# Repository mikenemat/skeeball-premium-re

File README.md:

# skeeball-premium-re

Reverse engineering of the Bay Tek **Skee-Ball Home Arcade Premium** electronics, and an open replacement for its main
board (A5CB25502 Rev 2.2).

The replacement board, **SBC-1**, is a drop-in swap: the same outline, mounting holes and harness connector positions as
the stock board, so the machine's existing wiring plugs straight in. On top of the stock functions it adds wired
Ethernet, so several lanes can share high scores and play together.

| Folder | What |
|---|---|
| [`hardware/`](hardware/) | SBC-1: KiCad 10 project, design-as-code scripts, BOM, routed 4-layer board, manufacturing files, design records |
| [software/](software/) | ARM image-analysis tools and synthetic tests |

## SBC-1 at a glance
- **MCU:** Raspberry Pi RP2350B with 16 MB QSPI flash.
- **Network:** WIZnet W5500 10/100 Ethernet (HanRun magjack).
- **Audio:** MAX98357A I2S class-D amplifier to the stock speaker.
- **Display:** USB host port for the stock score display.
- **Lights:** PWM low-side drivers on the existing RGB and playfield LED strips.
- **Power:** protected 5 V input (TVS, eFuse, resettable fuses).
- **Debug:** USB-C serial console and SWD.
- **Setup:** lane-ID DIP switch, status LEDs.
- **PCB:** 4-layer, 116.68 x 85.73 mm, assembled by JLCPCB (all parts from JLC stock).

**Status:** the first batch of boards is in production. Firmware for the new board is an original implementation and
is not published yet. See [`hardware/README.md`](hardware/README.md) for the project layout, how to regenerate
everything, and what is deliberately not in the repository. See [`hardware/docs/BRINGUP.md`](hardware/docs/BRINGUP.md)
for first power-up.

## Notes
- This is an independent hobby project. It is not affiliated with or endorsed by Bay Tek Entertainment. Skee-Ball is a
  trademark of its owner.
- The tracked repository contains no Bay Tek firmware, binaries or decompiled code. Stock-board facts here come from
  measurements, photos and continuity tests of the owner's own machines.
- Third-party datasheets and vendor 3D models are not redistributed. The setup notes in `hardware/README.md` say
  how to fetch them.

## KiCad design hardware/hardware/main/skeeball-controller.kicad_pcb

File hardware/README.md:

# SBC-1 - Skee-Ball lane controller

Networked drop-in replacement for the Bay Tek **A5CB25502 Rev 2.2** main board of the Skee-Ball Home Arcade Premium:
RP2350B + 16 MB QSPI flash, WIZnet W5500 wired Ethernet, MAX98357A I2S class-D audio, USB host port for the stock
display, protected 5 V input (TVS + eFuse), PWM light drivers, USB-C debug console, lane-ID DIP. Same outline, holes and
harness connector positions as the stock board.

**Status (2026-10-29):** ordered. Five boards are in production at JLCPCB (4-layer, Economic PCBA). The KiCad board in
`hardware/main/` is the build: routed with 0 open connections and DRC clean. `fab/release-2026-10-27c/` is the
manufacturing record (Gerbers, drills, JLC BOM and CPL). Bring-up instructions are in `docs/BRINGUP.md`. The firmware is
a separate, original implementation (not in this folder yet).

| Path | What |
|---|---|
| `docs/ARCHITECTURE.md` | requirements, I/O + GPIO map, MCU comparison, every block's reference + deviations, cost |
| `docs/MEASUREMENTS_NEEDED.md` | the caliper measurements / confirmations the layout needs |
| `docs/PLACEMENT_PLAN.md` | footprints, function groups, the RJ45 zone study |
| `docs/ORDERING.md` | BOM with LCSC codes, JLC stock, price, check date (generated) |
| `docs/WORK_STATE.md` | live state + next steps; `RUNNING-LOG.md`, `QA_LOG.md`, `DECISIONS.md` |
| `scripts/design.py` | design of record (parts, nets, references) |
| `hardware/main/` | KiCad 10 project: generated schematic (6 sheets) and the routed 4-layer board |
| `hardware/lib/` | project symbols (`skeeball.kicad_sym`) and footprints (`skeeball.pretty`) |
| `bom/bom.json`, `bom/bom.html` | single-writer BOM + viewer (`python -m http.server` in `bom/`, open bom.html) |
| `renders/` | schematic PDF, footprint / placement renders, final board renders (`renders/pcb/final-2026-10-27b/`) |
| `fab/release-2026-10-27c/` | manufacturing record: Gerber + drill zip, JLC BOM, JLC CPL (rotations fitted to JLC footprints) |
| `tools/pfr2/` | the autorouter and its gate / cleanup tools used for the copper |
| `datasheets/` | vendor documents used (not committed: download them from the manufacturers) |

## Setup (what is not in the repository)
These are git-ignored, because they are third-party, machine-specific or regenerable:
- `datasheets/`: manufacturer PDFs referenced in `design.py` notes and `docs/ARCHITECTURE.md`. Download them from the
  vendors.
- `hardware/lib/3d/vendor/`: the vendor STEP models. `python scripts/vendor_models.py` fetches them by JLC part number.
  The project's own envelope models (`hardware/lib/3d/*.wrl`) are committed.
- `tools/pylib/`: shapely + numpy for KiCad's bundled Python (KiCad 10 ships without shapely). Install them with
  `"C:/Program Files/KiCad/10.0/bin/python.exe" -m pip install --target tools/pylib shapely==2.1.2 numpy`.
- `bom/.jlc_api_cache/`, `bom/easyeda_cache/`: JLC / EasyEDA API caches, rebuilt on demand.
- `.runtime/`: router runs, gate outputs, scratch boards and backups.
- `scripts/scan_extract.py` needs the 300 dpi scan of the stock board's bottom side (not published). Set `SKEEBALL_SCAN`
  to its path. Its measured output is committed in `docs/records/scan_extract/`.

Tool versions: KiCad 10.0.6 (kicad-cli + its Python for `pcbnew` scripts), CPython 3.13 with numpy, scipy, pillow,
shapely, cairosvg and kicad-sch-api 0.5.5.

## Regenerate (CPython 3.13, KiCad 10.0.6)
```
cd scripts
python symgen.py                 # hardware/lib/skeeball.kicad_sym
python build_schematics.py       # schematic + KiCad ERC gate + netlist compare against design.py
python qa_footprints.py          # every footprint resolves (or is listed as pending with its reason)
python bom.py build && python bom.py refresh && python bom.py check && python bom.py report
python mcu_survey.py             # MCU option prices (docs/records/mcu_survey)
python fpgen.py                  # hardware/lib/skeeball.pretty (project footprints)
python scan_extract.py           # harness pad centres from the owner's 300 dpi bottom scan -> docs/records/scan_extract
python jlc_footprints.py C...     # JLC / EasyEDA footprint of a C-number -> bom/easyeda_cache (footprint cross-check)
python model_gen.py              # envelope 3D models for footprints without a KiCad model -> hardware/lib/3d
python photo_estimate.py && python render_placement.py   # placement plan + RJ45 study renders
python pcb_build.py              # board file: measured outline + 4 holes (+ SVG / PNG render)
"C:/Program Files/KiCad/10.0/bin/python.exe" place.py   # netlist import + placement + silk labels + KiCad DRC
"C:/Program Files/KiCad/10.0/bin/kicad-cli.exe" sch export pdf -o ../renders/schematic/skeeball-controller-schematic.pdf ../hardware/main/skeeball-controller.kicad_sch
```
Scripts reused from the owner's earlier din-relay-8ch project: `jlc_api.py` (unchanged), `netlist_core.py`, `gen_schematic.py`,
`qa_netlist.py`, `symgen.py` (library name / label direction / field placement adapted), the build -> ERC -> netlist QA
flow and the one-JSON / one-writer BOM.

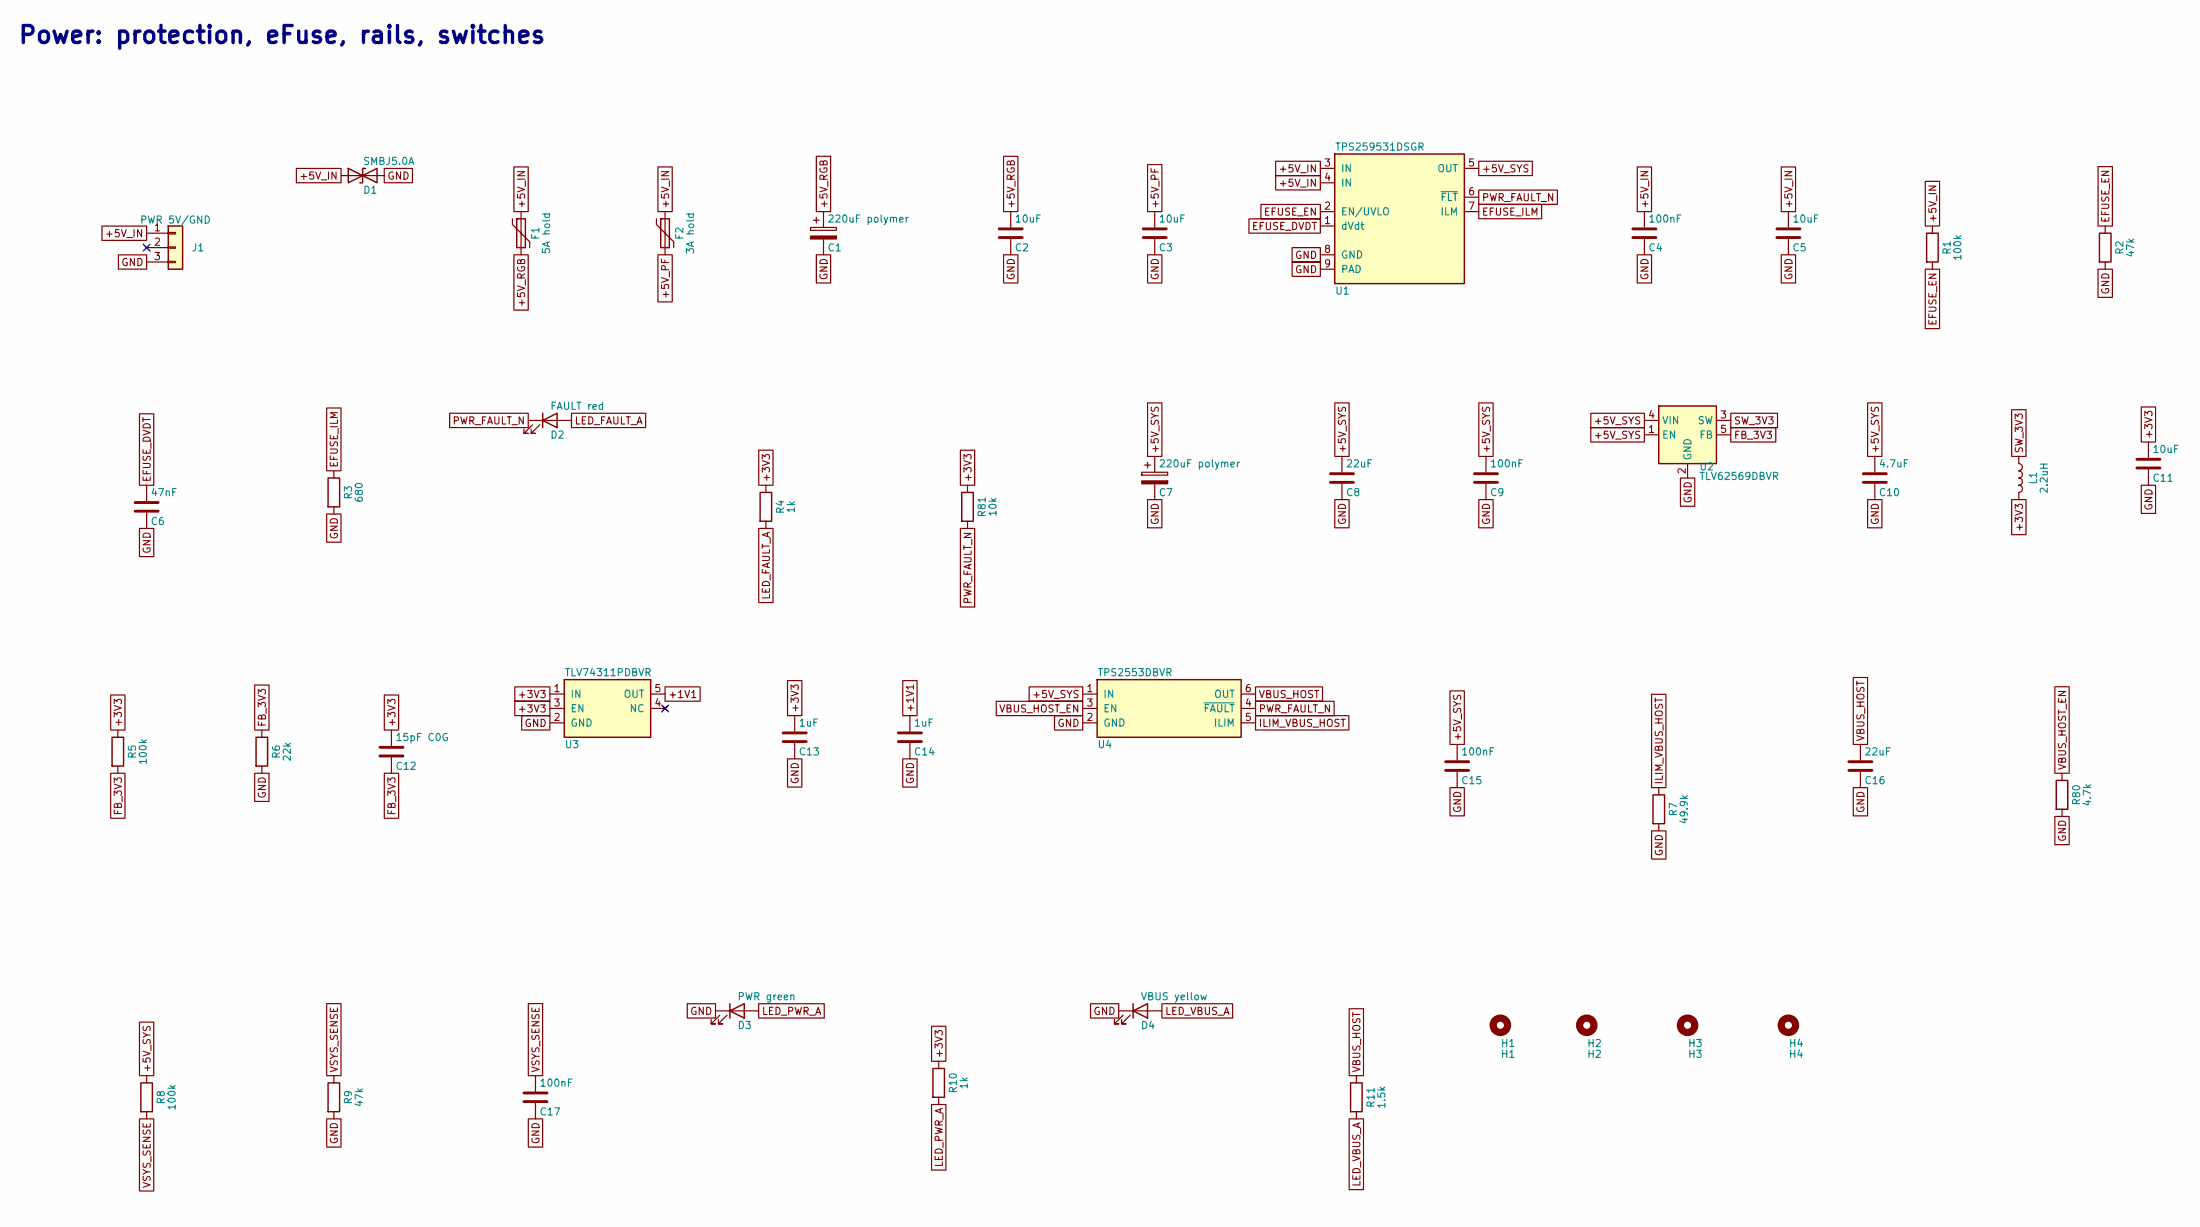
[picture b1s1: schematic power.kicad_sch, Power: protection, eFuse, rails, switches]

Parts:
C1, C7: 220uF polymer; CP_Elec_6.3x5.9; MPN OVZ221M1ATR-0606
C2, C3, C5, C11: 10uF; C_0805_2012Metric; MPN CL21A106KAYNNNE
C4, C9, C15, C17: 100nF; C_0603_1608Metric; MPN CC0603KRX7R9BB104
C6: 47nF; C_0603_1608Metric; MPN CL10B473KB8NNNC
C8, C16: 22uF; C_0805_2012Metric; MPN CL21A226MAQNNNE
C10: 4.7uF; C_0805_2012Metric; MPN CL21A475KAQNNNE
C12: 15pF C0G; C_0603_1608Metric; MPN CL10C150JB8NNNC
C13, C14: 1uF; C_0603_1608Metric; MPN CL10A105KB8NNNC
D1: SMBJ5.0A; D_SMB; MPN SMBJ5.0A; LCSC C83333
D2: FAULT red; LED_0603_1608Metric; MPN KT-0603R; LCSC C2286
D3: PWR green; LED_0603_1608Metric; MPN KT-0603G; LCSC C12624
D4: VBUS yellow; LED_0603_1608Metric; MPN NCD0603Y1; LCSC C84268
F1: 5A hold; Fuse_2920_7451Metric; MPN 2920L500/16MR; LCSC C207091
F2: 3A hold; Fuse_1812_4532Metric; MPN 1812L300MR; LCSC C127824
H1: H1; MountingHole_3.57mm
H2: H2; MountingHole_3.57mm
H3: H3; MountingHole_3.57mm
H4: H4; MountingHole_3.57mm
J1: PWR 5V/GND; Molex_Mini-Fit_Jr_39-30-3035_1x03_P4.20mm_Horizontal; MPN 39303035; LCSC C505179
L1: 2.2uH; L_Sunlord_SWPA4030S; MPN SWPA4030S2R2MT; LCSC C36409
R1, R5, R8: 100k; R_0603_1608Metric; tolerance 1%; MPN 0603WAF1003T5E
R2, R9: 47k; R_0603_1608Metric; tolerance 1%; MPN 0603WAF4702T5E
R3: 680; R_0603_1608Metric; tolerance 1%; MPN 0603WAF6800T5E
R4, R10: 1k; R_0603_1608Metric; tolerance 1%; MPN 0603WAF1001T5E
R6: 22k; R_0603_1608Metric; tolerance 1%; MPN 0603WAF2202T5E
R7: 49.9k; R_0603_1608Metric; tolerance 1%; MPN 0603WAF4992T5E
R11: 1.5k; R_0603_1608Metric; tolerance 1%; MPN 0603WAF1501T5E
R80: 4.7k; R_0603_1608Metric; tolerance 1%; MPN 0603WAF4701T5E
R81: 10k; R_0603_1608Metric; tolerance 1%; MPN 0603WAF1002T5E
U1: TPS259531DSGR; Texas_DSG0008A_WSON-8-1EP_2x2mm_P0.5mm_EP0.9x1.6mm; MPN TPS259531DSGR; LCSC C2155674
U2: TLV62569DBVR; SOT-23-5; MPN TLV62569DBVR; LCSC C141836
U3: TLV74311PDBVR; SOT-23-5; MPN TLV74311PDBVR; LCSC C485147
U4: TPS2553DBVR; SOT-23-6; MPN TPS2553DBVR; LCSC C55266

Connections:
+1V1: C14.1, U3.5 (OUT); also elsewhere on the board
+3V3: C11.1, C12.1, C13.1, L1.2, R4.1, R5.1, R10.1, R81.1, U3.1 (IN), U3.3 (EN); also elsewhere on the board
+5V_IN: C4.1, C5.1, D1.1 (A1), F1.1, F2.1, J1.1, R1.1, U1.3 (IN), U1.4 (IN)
+5V_PF: C3.1, F2.2; also elsewhere on the board
+5V_RGB: C1.1, C2.1, F1.2; also elsewhere on the board
+5V_SYS: C7.1, C8.1, C9.1, C10.1, C15.1, R8.1, U1.5 (OUT), U2.1 (EN), U2.4 (VIN), U4.1 (IN); also elsewhere on the board
EFUSE_DVDT: C6.1, U1.1 (dVdt)
EFUSE_EN: R1.2, R2.1, U1.2 (EN/UVLO)
EFUSE_ILM: R3.1, U1.7 (ILM)
FB_3V3: C12.2, R5.2, R6.1, U2.5 (FB)
GND: C1.2, C2.2, C3.2, C4.2, C5.2, C6.2, C7.2, C8.2, C9.2, C10.2, C11.2, C13.2, C14.2, C15.2, C16.2, C17.2, D1.2 (A2), D3.1 (K), D4.1 (K), J1.3, R2.2, R3.2, R6.2, R7.2, R9.2, R80.2, U1.8 (GND), U1.9 (PAD), U2.2 (GND), U3.2 (GND), U4.2 (GND); also elsewhere on the board
ILIM_VBUS_HOST: R7.1, U4.5 (ILIM)
LED_FAULT_A: D2.2 (A), R4.2
LED_PWR_A: D3.2 (A), R10.2
LED_VBUS_A: D4.2 (A), R11.2
PWR_FAULT_N: D2.1 (K), R81.2, U1.6 (~FLT), U4.4 (~FAULT); also elsewhere on the board
SW_3V3: L1.1, U2.3 (SW)
VBUS_HOST: C16.1, R11.1, U4.6 (OUT); also elsewhere on the board
VBUS_HOST_EN: R80.1, U4.3 (EN); also elsewhere on the board
VSYS_SENSE: C17.1, R8.2, R9.1; also elsewhere on the board

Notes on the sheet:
Power: protection, eFuse, rails, switches

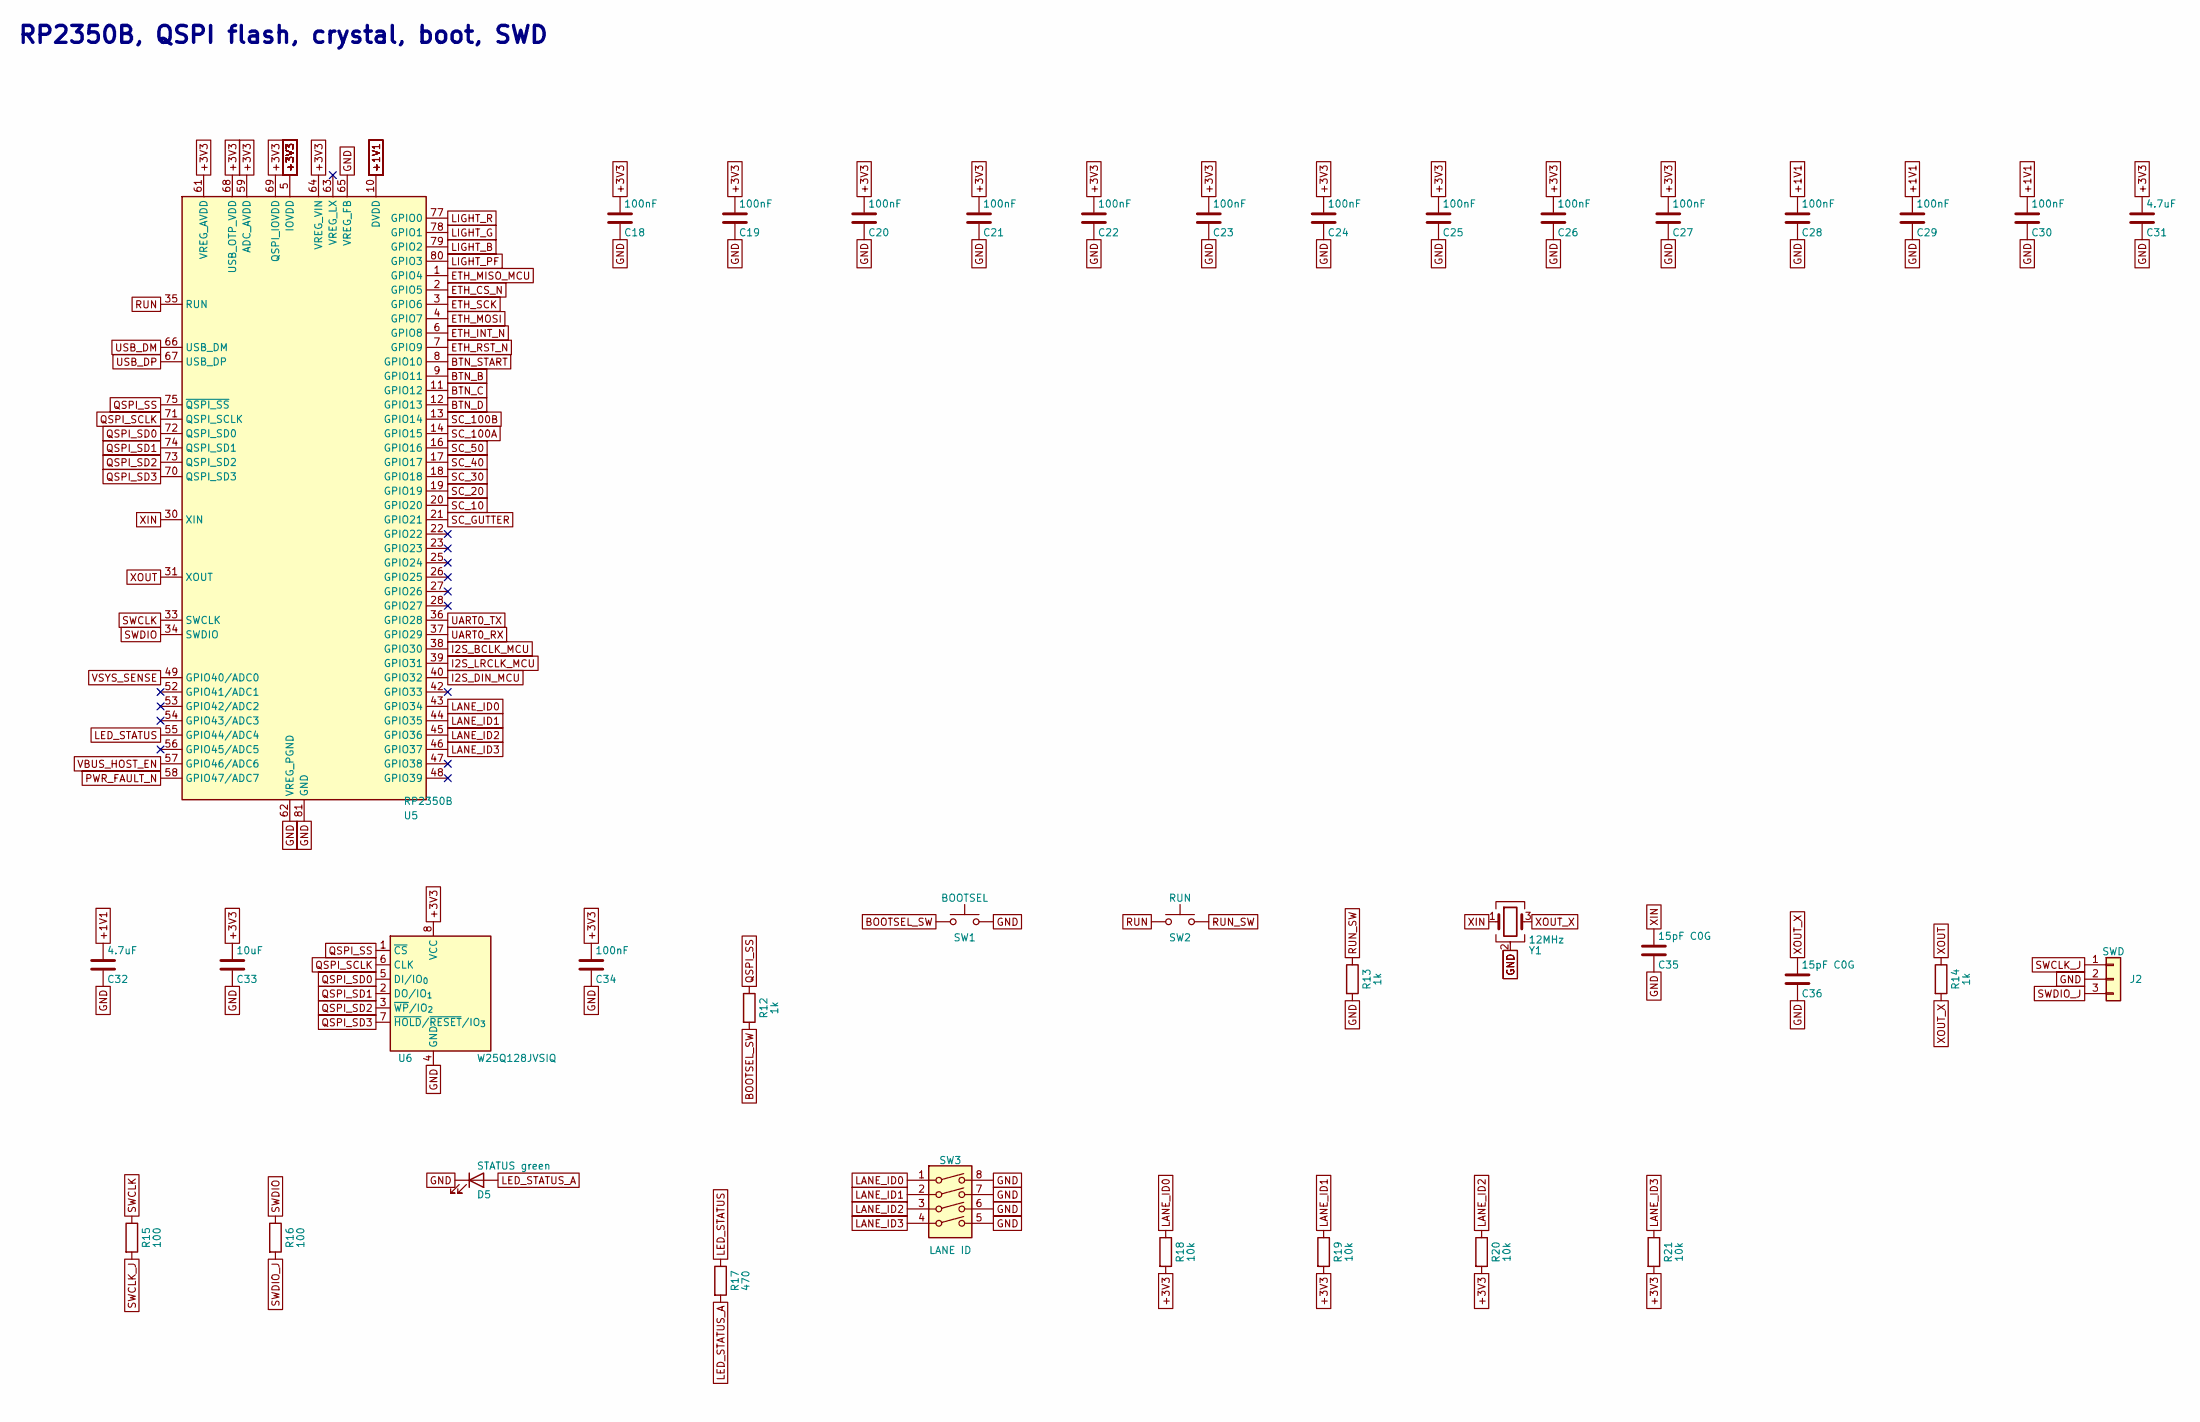
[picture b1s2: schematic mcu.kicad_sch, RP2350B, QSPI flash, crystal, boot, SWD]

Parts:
C18, C19, C20, C21, C22, C23, C24, C25, C26, C27, C28, C29, C30, C34: 100nF; C_0402_1005Metric; MPN CL05B104KO5NNNC
C31, C32: 4.7uF; C_0402_1005Metric; MPN CL05A475MP5NRNC
C33: 10uF; C_0805_2012Metric; MPN CL21A106KAYNNNE
C35, C36: 15pF C0G; C_0603_1608Metric; MPN CL10C150JB8NNNC
D5: STATUS green; LED_0603_1608Metric; MPN KT-0603G; LCSC C12624
J2: SWD; JST_SH_BM03B-SRSS-TB_1x03-1MP_P1.00mm_Vertical; MPN BM03B-SRSS-TB(LF)(SN); LCSC C160389
R12, R13, R14: 1k; R_0402_1005Metric; tolerance 1%; MPN 0402WGF1001TCE
R15, R16: 100; R_0402_1005Metric; tolerance 1%; MPN 0402WGF1000TCE
R17: 470; R_0603_1608Metric; tolerance 1%; MPN 0603WAF4700T5E
R18, R19, R20, R21: 10k; R_0603_1608Metric; tolerance 1%; MPN 0603WAF1002T5E
SW1: BOOTSEL; SW_Push_1P1T_XKB_TS-1187A; MPN TS-1187A-B-A-B; LCSC C318884
SW2: RUN; SW_Push_1P1T_XKB_TS-1187A; MPN TS-1187A-B-A-B; LCSC C318884
SW3: LANE ID; SW_DIP_XKB_DSIC04LS-P; MPN DSIC04LS-P; LCSC C319038
U5: RP2350B; QFN-80-1EP_10x10mm_P0.4mm_EP3.4x3.4mm; MPN RP2350B; LCSC C42415655
U6: W25Q128JVSIQ; SOIC-8_5.3x5.3mm_P1.27mm; MPN W25Q128JVSIQ; LCSC C97521
Y1: 12MHz; Crystal_SMD_3225-4Pin_3.2x2.5mm; MPN ABM8-272-T3; LCSC C20625731

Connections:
+1V1: C28.1, C29.1, C30.1, C32.1, U5.10 (DVDD), U5.32 (DVDD), U5.51 (DVDD); also elsewhere on the board
+3V3: C18.1, C19.1, C20.1, C21.1, C22.1, C23.1, C24.1, C25.1, C26.1, C27.1, C31.1, C33.1, C34.1, R18.2, R19.2, R20.2, R21.2, U5.5 (IOVDD), U5.15 (IOVDD), U5.24 (IOVDD), U5.29 (IOVDD), U5.41 (IOVDD), U5.50 (IOVDD), U5.59 (ADC_AVDD), U5.60 (IOVDD), U5.61 (VREG_AVDD), U5.64 (VREG_VIN), U5.68 (USB_OTP_VDD), U5.69 (QSPI_IOVDD), U5.76 (IOVDD), U6.8 (VCC); also elsewhere on the board
BOOTSEL_SW: R12.2, SW1.1
BTN_B: U5.9 (GPIO11); also elsewhere on the board
BTN_C: U5.11 (GPIO12); also elsewhere on the board
BTN_D: U5.12 (GPIO13); also elsewhere on the board
BTN_START: U5.8 (GPIO10); also elsewhere on the board
ETH_CS_N: U5.2 (GPIO5); also elsewhere on the board
ETH_INT_N: U5.6 (GPIO8); also elsewhere on the board
ETH_MISO_MCU: U5.1 (GPIO4); also elsewhere on the board
ETH_MOSI: U5.4 (GPIO7); also elsewhere on the board
ETH_RST_N: U5.7 (GPIO9); also elsewhere on the board
ETH_SCK: U5.3 (GPIO6); also elsewhere on the board
GND: C18.2, C19.2, C20.2, C21.2, C22.2, C23.2, C24.2, C25.2, C26.2, C27.2, C28.2, C29.2, C30.2, C31.2, C32.2, C33.2, C34.2, C35.2, C36.2, D5.1 (K), J2.2, R13.2, SW1.2, SW3.5, SW3.6, SW3.7, SW3.8, U5.62 (VREG_PGND), U5.65 (VREG_FB), U5.81 (GND), U6.4 (GND), Y1.2 (G), Y1.4 (G); also elsewhere on the board
I2S_BCLK_MCU: U5.38 (GPIO30); also elsewhere on the board
I2S_DIN_MCU: U5.40 (GPIO32); also elsewhere on the board
I2S_LRCLK_MCU: U5.39 (GPIO31); also elsewhere on the board
LANE_ID0: R18.1, SW3.1, U5.43 (GPIO34)
LANE_ID1: R19.1, SW3.2, U5.44 (GPIO35)
LANE_ID2: R20.1, SW3.3, U5.45 (GPIO36)
LANE_ID3: R21.1, SW3.4, U5.46 (GPIO37)
LED_STATUS: R17.1, U5.55 (GPIO44/ADC4)
LED_STATUS_A: D5.2 (A), R17.2
LIGHT_B: U5.79 (GPIO2); also elsewhere on the board
LIGHT_G: U5.78 (GPIO1); also elsewhere on the board
LIGHT_PF: U5.80 (GPIO3); also elsewhere on the board
LIGHT_R: U5.77 (GPIO0); also elsewhere on the board
PWR_FAULT_N: U5.58 (GPIO47/ADC7); also elsewhere on the board
QSPI_SCLK: U5.71 (QSPI_SCLK), U6.6 (CLK)
QSPI_SD0: U5.72 (QSPI_SD0), U6.5 (DI/IO_{0})
QSPI_SD1: U5.74 (QSPI_SD1), U6.2 (DO/IO_{1})
QSPI_SD2: U5.73 (QSPI_SD2), U6.3 (~WP/IO_{2})
QSPI_SD3: U5.70 (QSPI_SD3), U6.7 (~HOLD/~RESET/IO_{3})
QSPI_SS: R12.1, U5.75 (~QSPI_SS), U6.1 (~CS)
RUN: SW2.1, U5.35 (RUN)
RUN_SW: R13.1, SW2.2
SC_10: U5.20 (GPIO20); also elsewhere on the board
SC_20: U5.19 (GPIO19); also elsewhere on the board
SC_30: U5.18 (GPIO18); also elsewhere on the board
SC_40: U5.17 (GPIO17); also elsewhere on the board
SC_50: U5.16 (GPIO16); also elsewhere on the board
SC_100A: U5.14 (GPIO15); also elsewhere on the board
SC_100B: U5.13 (GPIO14); also elsewhere on the board
SC_GUTTER: U5.21 (GPIO21); also elsewhere on the board
SWCLK: R15.1, U5.33 (SWCLK)
SWCLK_J: J2.1, R15.2
SWDIO: R16.1, U5.34 (SWDIO)
SWDIO_J: J2.3, R16.2
UART0_RX: U5.37 (GPIO29); also elsewhere on the board
UART0_TX: U5.36 (GPIO28); also elsewhere on the board
USB_DM: U5.66 (USB_DM); also elsewhere on the board
USB_DP: U5.67 (USB_DP); also elsewhere on the board
VBUS_HOST_EN: U5.57 (GPIO46/ADC6); also elsewhere on the board
VSYS_SENSE: U5.49 (GPIO40/ADC0); also elsewhere on the board
XIN: C35.1, U5.30 (XIN), Y1.1
XOUT: R14.1, U5.31 (XOUT)
XOUT_X: C36.1, R14.2, Y1.3

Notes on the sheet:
RP2350B, QSPI flash, crystal, boot, SWD

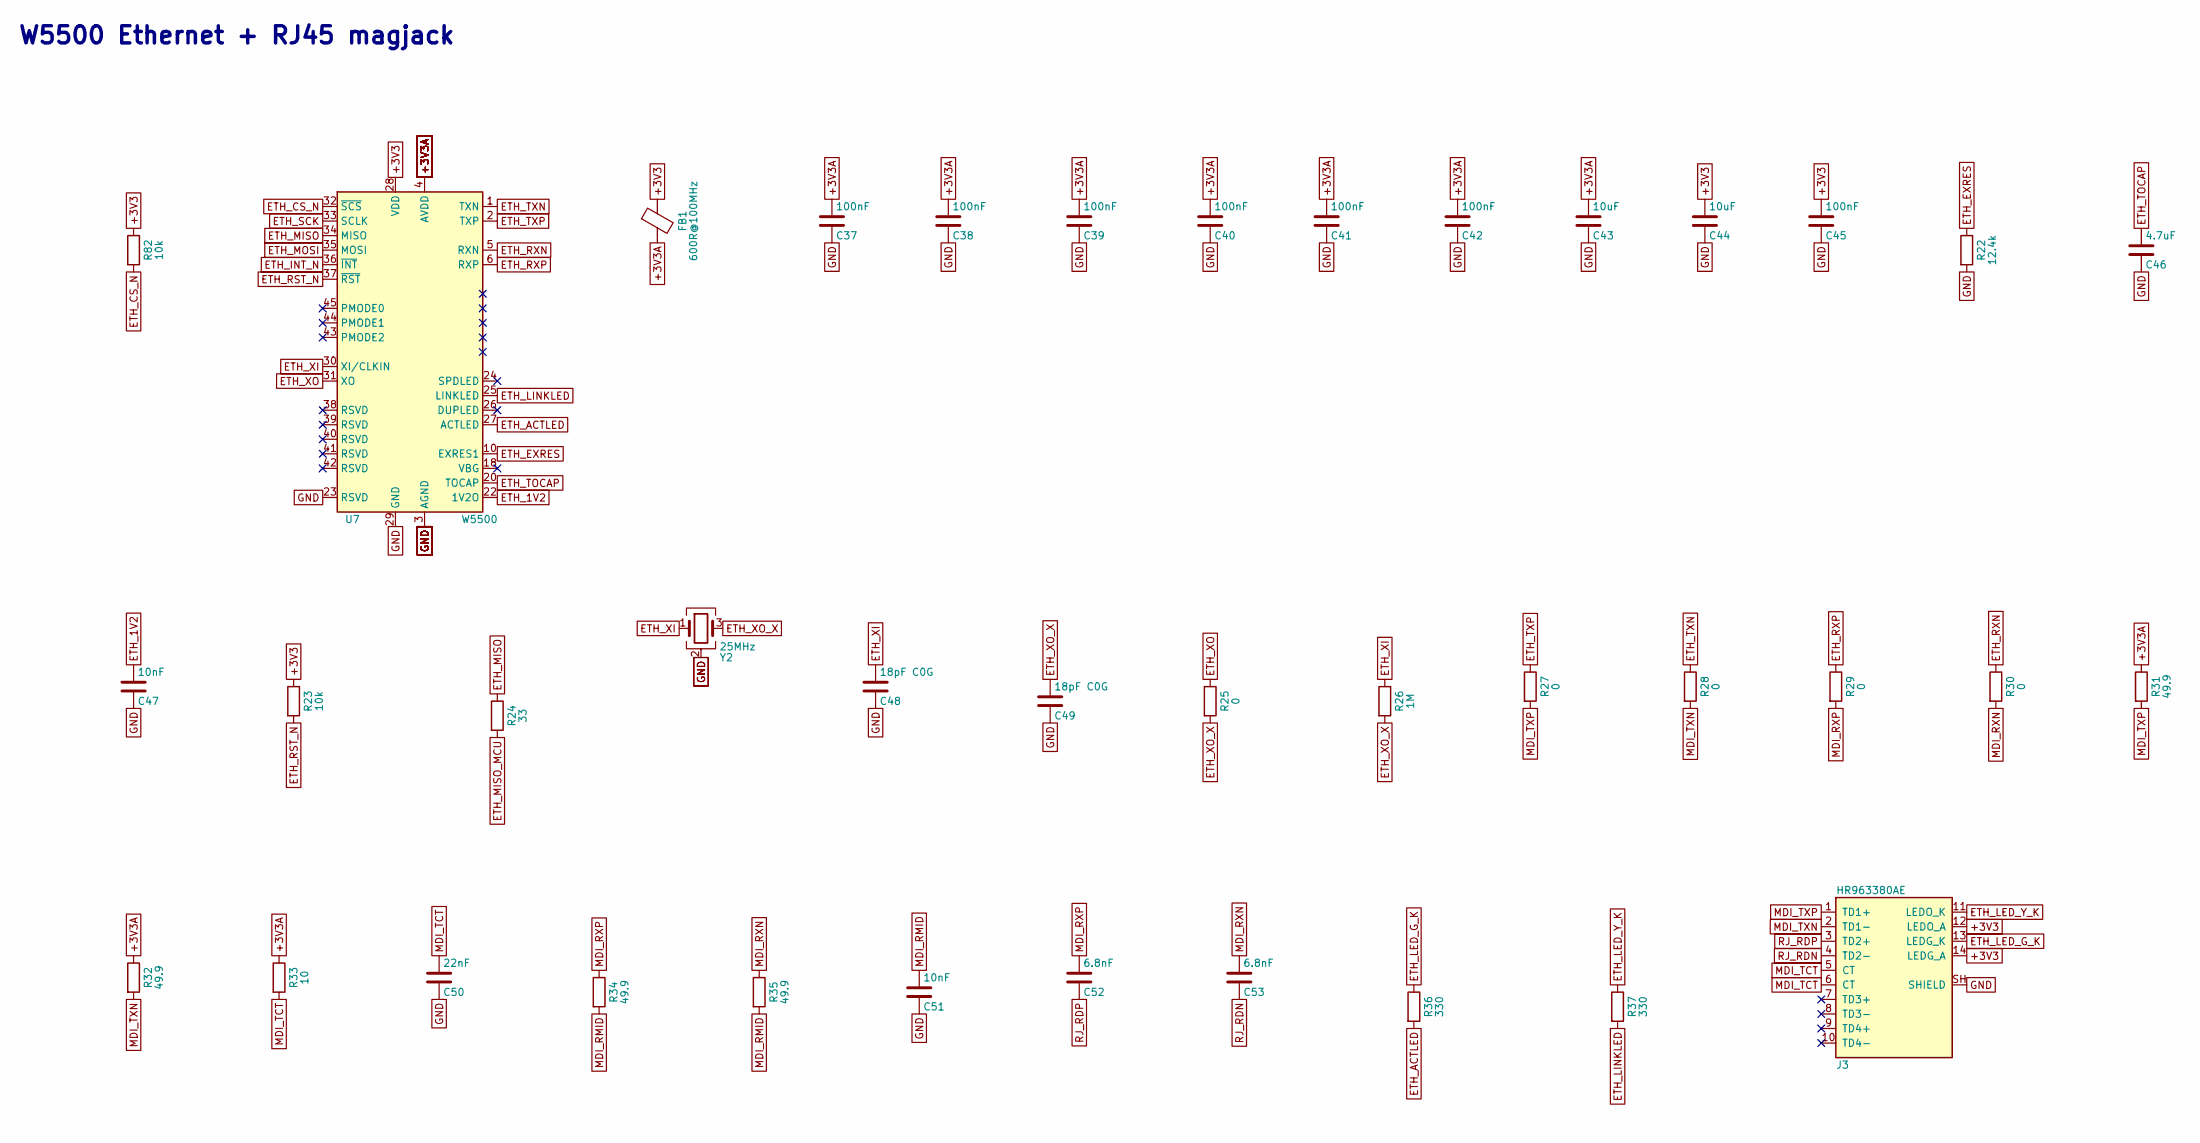
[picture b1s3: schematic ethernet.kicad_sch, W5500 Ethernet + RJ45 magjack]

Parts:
C37, C38, C39, C40, C41, C42, C45: 100nF; C_0603_1608Metric; MPN CC0603KRX7R9BB104
C43, C44: 10uF; C_0805_2012Metric; MPN CL21A106KAYNNNE
C46: 4.7uF; C_0805_2012Metric; MPN CL21A475KAQNNNE
C47, C51: 10nF; C_0603_1608Metric; MPN 0603B103K500NT
C48, C49: 18pF C0G; C_0603_1608Metric; MPN CL10C180JB8NNNC
C50: 22nF; C_0603_1608Metric; MPN CL10B223KB8NNNC
C52, C53: 6.8nF; C_0603_1608Metric; MPN 0603B682K500NT
FB1: 600R@100MHz; L_0805_2012Metric; MPN GZ2012D601TF; LCSC C1017
J3: HR963380AE; RJ45_HanRun_HR963380AE_Vertical; MPN HR963380AE; LCSC C19724763
R22: 12.4k; R_0603_1608Metric; tolerance 1%; MPN 0603WAF1242T5E
R23, R82: 10k; R_0603_1608Metric; tolerance 1%; MPN 0603WAF1002T5E
R24: 33; R_0603_1608Metric; tolerance 1%; MPN 0603WAF330JT5E
R25, R27, R28, R29, R30: 0; R_0603_1608Metric; tolerance 1%; MPN 0603WAF0000T5E
R26: 1M; R_0603_1608Metric; tolerance 1%; MPN 0603WAF1004T5E
R31, R32, R34, R35: 49.9; R_0603_1608Metric; tolerance 1%; MPN 0603WAF499JT5E
R33: 10; R_0603_1608Metric; tolerance 1%; MPN 0603WAF100JT5E
R36, R37: 330; R_0603_1608Metric; tolerance 1%; MPN 0603WAF3300T5E
U7: W5500; LQFP-48_7x7mm_P0.5mm; MPN W5500; LCSC C32843
Y2: 25MHz; Crystal_SMD_3225-4Pin_3.2x2.5mm; MPN X322525MOB4SI; LCSC C9006

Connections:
+3V3: C44.1, C45.1, FB1.1, J3.12 (LEDO_A), J3.14 (LEDG_A), R23.1, R82.1, U7.28 (VDD); also elsewhere on the board
+3V3A: C37.1, C38.1, C39.1, C40.1, C41.1, C42.1, C43.1, FB1.2, R31.1, R32.1, R33.1, U7.4 (AVDD), U7.8 (AVDD), U7.11 (AVDD), U7.15 (AVDD), U7.17 (AVDD), U7.21 (AVDD)
ETH_1V2: C47.1, U7.22 (1V2O)
ETH_ACTLED: R36.2, U7.27 (ACTLED)
ETH_CS_N: R82.2, U7.32 (~SCS); also elsewhere on the board
ETH_EXRES: R22.1, U7.10 (EXRES1)
ETH_INT_N: U7.36 (~INT); also elsewhere on the board
ETH_LED_G_K: J3.13 (LEDG_K), R36.1
ETH_LED_Y_K: J3.11 (LEDO_K), R37.1
ETH_LINKLED: R37.2, U7.25 (LINKLED)
ETH_MISO: R24.1, U7.34 (MISO)
ETH_MISO_MCU: R24.2; also elsewhere on the board
ETH_MOSI: U7.35 (MOSI); also elsewhere on the board
ETH_RST_N: R23.2, U7.37 (~RST); also elsewhere on the board
ETH_RXN: R30.1, U7.5 (RXN)
ETH_RXP: R29.1, U7.6 (RXP)
ETH_SCK: U7.33 (SCLK); also elsewhere on the board
ETH_TOCAP: C46.1, U7.20 (TOCAP)
ETH_TXN: R28.1, U7.1 (TXN)
ETH_TXP: R27.1, U7.2 (TXP)
ETH_XI: C48.1, R26.1, U7.30 (XI/CLKIN), Y2.1
ETH_XO: R25.1, U7.31 (XO)
ETH_XO_X: C49.1, R25.2, R26.2, Y2.3
GND: C37.2, C38.2, C39.2, C40.2, C41.2, C42.2, C43.2, C44.2, C45.2, C46.2, C47.2, C48.2, C49.2, C50.2, C51.2, J3.SH (SHIELD), R22.2, U7.3 (AGND), U7.9 (AGND), U7.14 (AGND), U7.16 (AGND), U7.19 (AGND), U7.23 (RSVD), U7.29 (GND), U7.48 (AGND), Y2.2 (G), Y2.4 (G); also elsewhere on the board
MDI_RMID: C51.1, R34.2, R35.2
MDI_RXN: C53.1, R30.2, R35.1
MDI_RXP: C52.1, R29.2, R34.1
MDI_TCT: C50.1, J3.5 (CT), J3.6 (CT), R33.2
MDI_TXN: J3.2 (TD1-), R28.2, R32.2
MDI_TXP: J3.1 (TD1+), R27.2, R31.2
RJ_RDN: C53.2, J3.4 (TD2-)
RJ_RDP: C52.2, J3.3 (TD2+)

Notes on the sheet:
W5500 Ethernet + RJ45 magjack

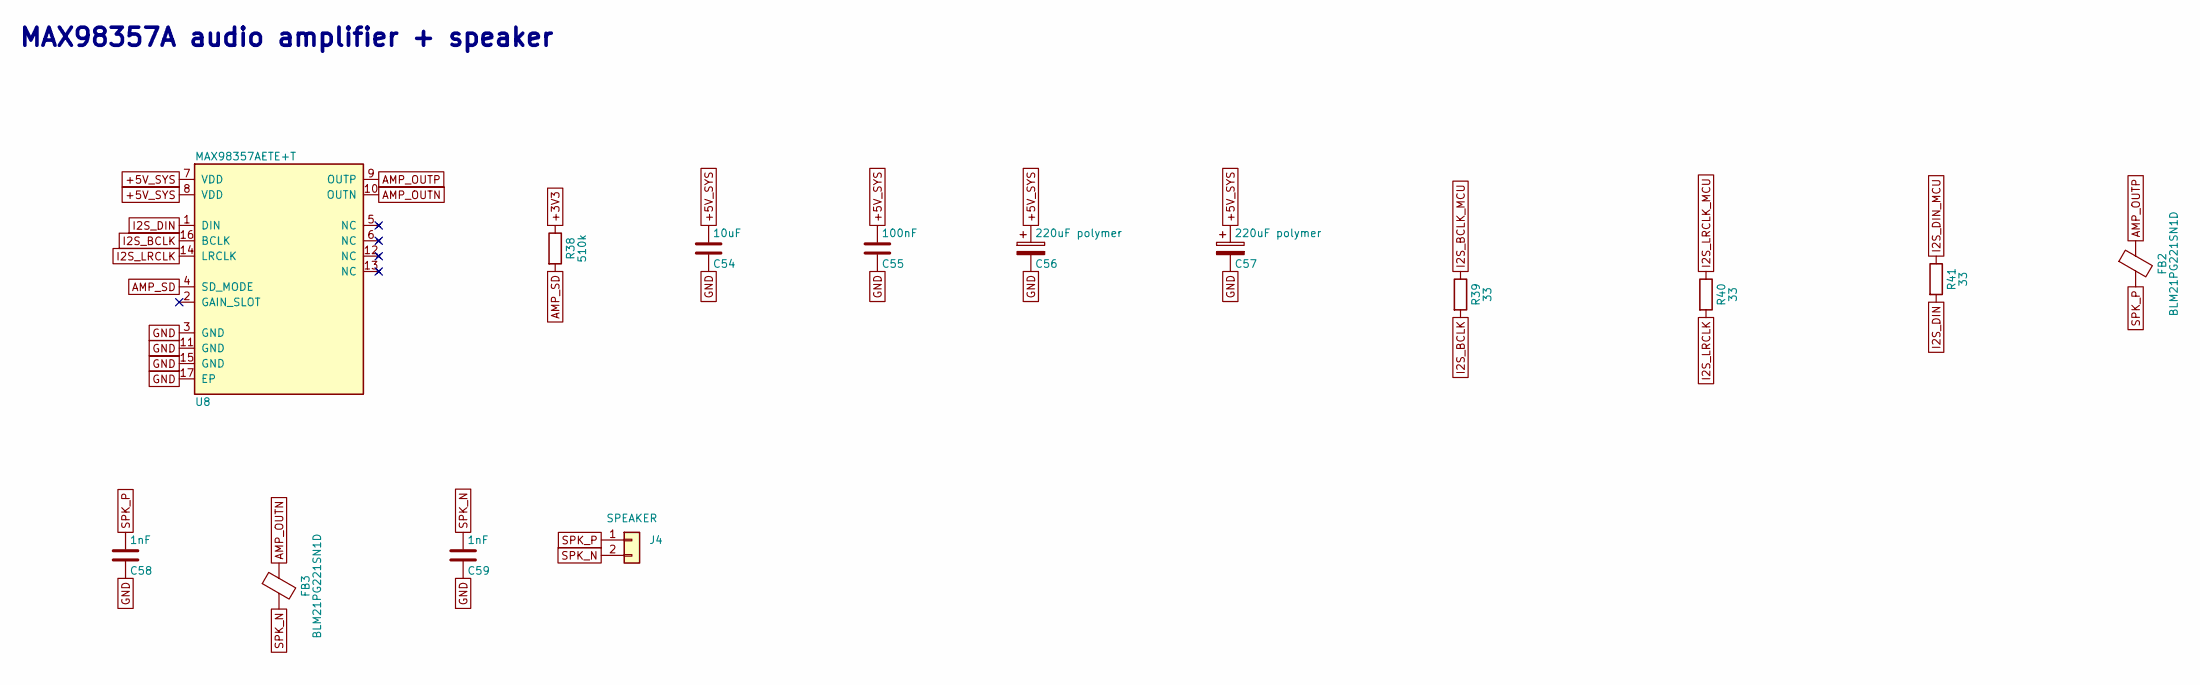
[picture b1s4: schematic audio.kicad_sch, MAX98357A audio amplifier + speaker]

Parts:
C54: 10uF; C_0805_2012Metric; MPN CL21A106KAYNNNE
C55: 100nF; C_0603_1608Metric; MPN CC0603KRX7R9BB104
C56, C57: 220uF polymer; CP_Elec_6.3x5.9; MPN OVZ221M1ATR-0606
C58, C59: 1nF; C_0603_1608Metric; MPN CL10B102KB8NNNC
FB2, FB3: BLM21PG221SN1D; L_0805_2012Metric; MPN BLM21PG221SN1D; LCSC C85840
J4: SPEAKER; Molex_Mini-Fit_Jr_5569-02A2_2x01_P4.20mm_Horizontal; MPN 39300020; LCSC C240831
R38: 510k; R_0603_1608Metric; tolerance 1%; MPN 0603WAF5103T5E
R39, R40, R41: 33; R_0603_1608Metric; tolerance 1%; MPN 0603WAF330JT5E
U8: MAX98357AETE+T; TQFN-16-1EP_3x3mm_P0.5mm_EP1.23x1.23mm; MPN MAX98357AETE+T; LCSC C910544

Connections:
+3V3: R38.1; also elsewhere on the board
+5V_SYS: C54.1, C55.1, C56.1, C57.1, U8.7 (VDD), U8.8 (VDD); also elsewhere on the board
AMP_OUTN: FB3.1, U8.10 (OUTN)
AMP_OUTP: FB2.1, U8.9 (OUTP)
AMP_SD: R38.2, U8.4 (SD_MODE)
GND: C54.2, C55.2, C56.2, C57.2, C58.2, C59.2, U8.3 (GND), U8.11 (GND), U8.15 (GND), U8.17 (EP); also elsewhere on the board
I2S_BCLK: R39.2, U8.16 (BCLK)
I2S_BCLK_MCU: R39.1; also elsewhere on the board
I2S_DIN: R41.2, U8.1 (DIN)
I2S_DIN_MCU: R41.1; also elsewhere on the board
I2S_LRCLK: R40.2, U8.14 (LRCLK)
I2S_LRCLK_MCU: R40.1; also elsewhere on the board
SPK_N: C59.1, FB3.2, J4.2
SPK_P: C58.1, FB2.2, J4.1

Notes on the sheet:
MAX98357A audio amplifier + speaker
